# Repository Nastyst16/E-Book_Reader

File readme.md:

# OpenBook

## Project Overview
OpenBook is an open-source e-book reader designed to be cost-effective and accessible. The goal of this project is to develop the hardware required for mass production based on system architecture specifications. This includes designing the schematic, PCB layout, and 3D models necessary for the device.

## Repository Structure
```
- Hardware
  |-- schematic (.sch)
  |-- PCB layout (.brd)
- Manufacturing
  |-- gerbers.zip
  |-- Bill of Materials
  |-- Pick and Place file
- Mechanical
  |-- 3D model of the device (.step)
  |-- Fusion360 file of the complete device
- Images
  |-- Rendered images of the PCB and device
- LICENSE
- README.md
```

## Hardware Overview
### Block Diagram

# Bill of Materials (BOM)

| 🔩 Component                                        | 🔗 Link                | 📄 Datasheet                        |
|--------------------------------------------------|-----------------------------------|-----------------------------------|
| ESP32-C6 WROOM-1-N8                              | [SnapMagic](https://www.snapeda.com/parts/ESP32-C6-WROOM-1-N8/Espressif+Systems/view-part/?ref=eda)         | [Datasheet](https://www.snapeda.com/parts/ESP32-C6-WROOM-1-N8/Espressif%20Systems/datasheet/)     |
| ESP32C6 Varistor 1812                            | [Mouser](https://ro.mouser.com/ProductDetail/EPCOS-TDK/B72520T0350K062?qs=dEfas%2FXlABIszF52uu7vrg%3D%3D)        | [Datasheet](https://www.tdk-electronics.tdk.com/inf/75/db/CTVS_14/Surge_protection_series.pdf)     |
| ESP32 WROVER 0805 Capacitor                      | [Mouser](https://ro.mouser.com/ProductDetail/KYOCERA-AVX/SD0805S020S1R0?qs=jCA%252BPfw4LHbpkAoSnwrdjw%3D%3D)         | [Datasheet](https://ro.mouser.com/datasheet/2/40/schottky-3165252.pdf)     |
| ESP32 WROVER BME680 Sensor                       | [SnapMagic](https://www.snapeda.com/parts/BME680/Bosch/view-part/?welcome=home)        | [Datasheet](https://www.snapeda.com/parts/BME680/Bosch%20Sensortec/datasheet/)     |
| ESP32 WROVER MCP73831 Power Management           | [Mouser](https://eu.mouser.com/ProductDetail/Microchip-Technology/MCP73831T-2ACI-OT?qs=yUQqVecv4qvbBQBGbHx0Mw%3D%3D)         | [Datasheet](https://eu.mouser.com/datasheet/2/268/MCP73831_Family_Data_Sheet_DS20001984H-3441711.pdf)     || ESP32 WROVER P-Channel MOSFET                    | [Component Search Engine](https://componentsearchengine.com/part-view/DMG2305UX-7/Diodes%20Incorporated)         | [Datasheet](https://www.diodes.com//assets/Datasheets/DMG2305UX.pdf)     |
| LED Chip 0603                                    | [SnapMagic](https://www.snapeda.com/parts/KP-1608SURCK/Kingbright/view-part/?ref=search&t=LED%200603)        | [Datasheet](https://www.snapeda.com/parts/KP-1608SURCK/Kingbright/datasheet/)     |
| SJ                                               | [GrabCad](https://grabcad.com/library/solder-jumpers-1)         | [Datasheet](https://www.youtube.com/watch?v=dQw4w9WgXcQ)     |
| LTSPICE Resistor 0402                            | [Component Search Engine](https://componentsearchengine.com/part-view/R0402%201%25%20100%20K%20(RC0402FR-07100KL)/YAGEO)        | [Datasheet](https://www.yageo.com/upload/media/product/products/datasheet/rchip/PYu-RC_Group_51_RoHS_L_12.pdf)     |
| RCL CPOL 3528                                    | [SnapMagic](https://www.snapeda.com/parts/TAJB475K025RNJ/AVX/view-part/?ref=dk&t=capacitor%203528&con_ref=None)        | [Datasheet](https://s3.amazonaws.com/snapeda/datasheet/TAJB475K025RNJ_AVX.pdf)     |
| 112A-TAAR-R03                                    | [Comet](https://store.comet.srl.ro/Catalogue/Product/43497/)         | [Datasheet](https://store.comet.bg/download-file.php?id=27596)     |
| 744043680 IND                                    | [Mouser](https://eu.mouser.com/ProductDetail/Wurth-Elektronik/744043680?qs=PGXP4M47uW6VkZq%252BkzjrHA%3D%3D)        | [Datasheet](https://www.we-online.com/components/products/datasheet/744043680.pdf)     |
| BD5229G-TR                                       | [Component Search Engine](https://componentsearchengine.com/part-view/BD5229G-TR/ROHM%20Semiconductor)         | [Datasheet](https://datasheet.datasheetarchive.com/originals/distributors/Datasheets_SAMA/f2b9741ef86007909f138d561a359946.pdf)     |
| Custom Button                                    | [Panasonic](https://industry.panasonic.com/global/en/products/control/switch/light-touch/number/evqpuj02k)        | [Datasheet](https://industry.panasonic.com/global/en/downloads?tab=catalog&small_g_cd=203&part_no=EVQPUJ02K&q=RVZRUFVKMDJLJTdDMTMlN0MyMDMlN0MzNDU5JTdDMSU3QyU3QzIlN0M%3D)     |
| CPH3225A                                         | [SnapMagic](https://www.snapeda.com/parts/CPH3225A/Seiko+Instruments/view-part/?ref=eda)         | [Datasheet](https://www.snapeda.com/parts/CPH3225A/Seiko%20Instruments/datasheet/)     |
| DS3231SN RTC                                     | [SnapMagic](https://www.snapeda.com/parts/DS3231SN%23/Analog+Devices/view-part/?ref=eda)        | [Datasheet](https://www.snapeda.com/parts/DS3231SN%23/Analog%20Devices/datasheet/)     |
| FH34SRJ-24S-0.5SH Connector                      | [Component Search Engine](https://componentsearchengine.com/part-view/FH34SRJ-24S-0.5SH(99)/Hirose)        | [Datasheet](https://www.hirose.com/en/product/document?clcode=CL0580-1255-6-99&productname=FH34SRJ-24S-0.5SH(99)&series=FH34SRJ&documenttype=2DDrawing&lang=en&documentid=0000990903)     |
| MAX17048G+T10 Battery Fuel Gauge                 | [SnapMagic](https://www.snapeda.com/parts/MAX17048G+T10/Analog+Devices/view-part/?ref=eda)         | [Datasheet](https://www.snapeda.com/parts/MAX17048G+T10/Analog%20Devices/datasheet/)     |
| MBR0530 Schottky Diode                           | [SnapMagic](https://www.snapeda.com/parts/MBR0530/Onsemi/view-part/?ref=eda)        | [Datasheet](https://www.snapeda.com/parts/MBR0530/ON%20Semiconductor/datasheet/)     |
| PGB1010603MR Inductor                            | [SnapMagic](https://www.snapeda.com/parts/PGB1010603MR/Littelfuse/view-part/?ref=eda)         | [Datasheet](https://www.snapeda.com/parts/PGB1010603MR/Littelfuse%20Inc./datasheet/)     |
| QWIIC Connector                                  | [Mouser](https://eu.mouser.com/ProductDetail/Adafruit/4208?qs=PzGy0jfpSMtbScLbr0L5dw%3D%3D)        | [Datasheet](https://www.youtube.com/watch?v=dQw4w9WgXcQ)     |
| USB4110-GF-A USB Hub                             | [Component Search Engine](https://componentsearchengine.com/part-view/USB4110-GF-A/GCT%20(GLOBAL%20CONNECTOR%20TECHNOLOGY))         | [Datasheet](https://gct.co/files/drawings/usb4110.pdf)     |
| SI1308EDL-T1-GE3 MOSFET                          | [SnapMagic](https://www.snapeda.com/parts/SI1308EDL-T1-GE3/Vishay+Siliconix/view-part/?ref=eda)        | [Datasheet](https://www.youtube.com/watch?v=dQw4w9WgXcQ)     |
| TPTP20R                                          | [Comet](https://easyeda.com/component/7524403feb2642ac9f9f26dfb93ceacf)         | [Datasheet](https://easyeda.com/component/7524403feb2642ac9f9f26dfb93ceacf)     |
| USBLC6-2SC6Y USB Surge Protection                | [SnapMagic](https://www.snapeda.com/parts/USBLC6-2SC6Y/STMicroelectronics/view-part/?ref=eda)        | [Datasheet](https://www.snapeda.com/parts/USBLC6-2SC6Y/STMicroelectronics/datasheet/)     |
| W25Q512JVEIQ Flash Memory                        | [SnapMagic](https://www.snapeda.com/parts/W25Q512JVEIQ/Winbond+Electronics/view-part/?ref=eda)         | [Datasheet](https://www.snapeda.com/parts/W25Q512JVEIQ/Winbond%20Electronics/datasheet/)     |
| XC6220A331MR-G Voltage Regulator                 | [Component Search Engine](https://componentsearchengine.com/part-view/XC6220A331MR-G/Torex)        | [Datasheet](https://product.torexsemi.com/system/files/series/xc6220.pdf)     |

# Hardware Functionality Overview

## 1. Battery
- **Model:** CELLEVIA BATTERIES LP584174  
- **Specifications:** 3.7V, 1800mAh  
- **Purpose:** Powers the entire device. The Li-Po battery is managed by a dedicated charging controller, which helps extend battery lifespan and provides protection against overcharging and deep discharge.

## 2. E-Paper Display
- **Model:** 7.5” e-Paper V2  
- **Revision:** 2.0 (2019/06/28)  
- **Description:** This display offers ultra-low power consumption, making it ideal for static text rendering. It communicates via an SPI interface and is powered through a low-dropout (LDO) voltage regulator.

## 3. ESP32 C6 Microcontroller
- **Function:** Acts as the main controller, handling communication between all peripherals including the display, sensors, storage modules, and more. It also provides Wi-Fi and Bluetooth connectivity.

## 4. BME688 Environmental Sensor
- **Interface:** I2C  
- **Functionality:** Measures temperature, humidity, pressure, and air quality. These readings can influence device behavior depending on environmental conditions.

## 5. RTC Module - DS3231SN
- **Interface:** I2C  
- **Purpose:** Maintains accurate date and time even when the device is powered off. Useful for timestamping, scheduling wake-ups, or saving user progress.

## 6. Li-Po Charging Controller - MCP73831T
- **Power Source:** USB-C  
- **Function:** Safely manages the charging of the Li-Po battery. Includes features that prevent overcharging and deep discharge. The USB-C port also allows for fast charging.

## 7. SD Card Module
- **Interface:** SPI  
- **Purpose:** Enables external file storage, such as e-books. It is essential for managing and accessing reading materials.

## 8. External NOR Flash (64MB)
- **Interface:** SPI  
- **Usage:** Provides additional memory space for application data and firmware.

## 9. Test Pads & Qwiic/Stemma QT Connectors
- **Functionality:** Test pads are used for debugging and quality control during development. The modular connectors support easy integration of sensors or peripherals over I2C or SPI.

## 10. LDO Voltage Regulator
- **Purpose:** Ensures a stable voltage supply to all hardware components, protecting them from fluctuations in input voltage.

---

## Communication Interfaces

- **GPIO:** Used for handling physical buttons such as power or reset.
- **USB-C:** Used for charging and PC connectivity.
- **I2C:** Connects components like the environmental sensor and RTC module.
- **SPI:** Used for high-speed data transfer with components like the display, SD card, and external flash.

---

# Power Consumption Overview

The following estimates reflect typical usage scenarios based on standard operating conditions.

## Battery
- **Voltage:** 3.7V  
- **Capacity:** 1800mAh  
- **Battery Life:** Varies based on power draw; under typical conditions, it can last several hours.

## ESP32 C6
- **Idle:** ~0.1mA  
- **Wi-Fi active:** ~200mA  
- **Bluetooth active:** ~150mA  
- **Max load:** ~350mA  
- **Estimated average:** 150mA

## E-Paper Display
- **Consumption during refresh:** 30–50mA  
- **Estimated average:** 40mA with infrequent updates

## BME688 Sensor
- **Typical draw:** 2mA

## DS3231SN RTC Module
- **Estimated draw:** 2mA

## MCP73831T Charger
- **Consumption during idle:** Negligible

## SD Card
- **Typical draw:** 10–15mA  
- **Estimated average:** 12mA

## NOR Flash
- **Active usage:** 20–30mA  
- **Estimated average:** 25mA

---

## Estimated Total Consumption (Typical Use)

| Component              | Current Draw (mA) |
|------------------------|-------------------|
| ESP32 (Wi-Fi active)   | 200mA             |
| E-Paper Display        | 40mA              |
| BME688 Sensor          | 2mA               |
| RTC Module             | 2mA               |
| SD Card                | 12mA              |
| NOR Flash              | 25mA              |
| **Total**              | **281mA**         |

---

## Battery Life Estimate

To estimate battery life:

 - Battery Life = Battery Capacity / Average Current Draw
 - Battery Life = 1800mAh / 281mA ≈ 6.41 hours

 ### Important Notes:
This estimate assumes continuous operation with Wi-Fi enabled, periodic display refreshes, and sensor readings. In practical use, battery life can be significantly extended through:

- Low-power sleep modes on the ESP32  
- Reducing display update frequency  
- Disabling unused modules or interfaces 

# ESP32-C6 Pin Usage Breakdown

This section outlines the pin configuration used in the current hardware design based on the ESP32-C6 microcontroller.

## Power Connections
- **3V3 (Pin 2 & top-right corner)** – Supplies 3.3V to the microcontroller and all connected peripherals.
- **GND (bottom-right corner)** – Ground reference for the entire system.

## Boot and Reset
- **GPIO8 (Pin 15, IO/BOOT)** – Used to enter bootloader mode; pulled low through a 10kΩ resistor.
- **RESET (Pin 3)** – Manual reset input for restarting the microcontroller.

## SPI Interface (E-Paper Display and Flash Memory)
- **MISO (Pin 27)** – SPI Master-In Slave-Out; receives data from connected devices.
- **MOSI (Pin 10)** – SPI Master-Out Slave-In; sends data to peripherals.
- **SCK (Pin 7)** – Serial clock line for SPI communication.
- **SS_SD (Pin 4)** – Likely used as Chip Select (CS) for the SD card module.
- **EPD_CS (Pin 11)** – Chip Select for the E-Paper Display.
- **FLASH_CS (Pin 12)** – Chip Select for the external NOR Flash.

## E-Paper Display Control
- **EPD_BUSY (Pin 26)** – Indicates when the display controller is processing a command.
- **EPD_DC (Pin 5)** – Data/Command control signal for the E-Paper interface.
- **EPD_RST (Pin 21)** – Reset pin for the E-Paper controller.
- **EPD_3V3_C (Pin 19)** – Likely used to control or enable power to the E-Paper display.

## I2C Interface (RTC and Environmental Sensors)
- **SDA (Pin 20)** – Data line for I2C communication.
- **SCL (Pin 21)** – Clock line for I2C communication.
- **I2C_PW (Pin 18)** – Controls power delivery to I2C-connected devices.
- **INT_RTC (Pin 8)** – Interrupt output from the RTC module.
- **RTC_RST (Pin 16)** – Reset input for the RTC chip.

## USB Interface
- **USB_D- (Pin 13)** and **USB_D+ (Pin 14)** – Differential data lines for USB communication.

## UART Interface
- **TX (Pin 25)** – UART transmit pin used for serial output.
- **RX (Pin 24)** – UART receive pin used for serial input.

## Additional GPIOs
- **IO_CHANGE (Pin 23)** – Custom GPIO, possibly used for interrupts or status signals from external hardware.

---

### Pin Mapping Considerations

This pin configuration is chosen to balance performance and modularity:
- The SPI bus supports high-speed data exchange with both the E-Paper Display and external flash memory.
- The I2C bus is reserved for lower-speed peripherals, such as the RTC and environmental sensors.
- Dedicated control signals for the display enable precise handling of rendering operations.
- UART is available for serial debugging or external communication.
- Power, reset, and enable signals are placed for ease of access and stability in the overall system layout.

## Design Constraints
- **PCB Dimensions**: Must fit within the predefined casing
- **Power Traces**: Width = 0.3mm, Data traces = 0.15mm minimum
- **No Right-Angle Traces**: Ensure smooth signal flow
- **Decoupling Capacitors**: 100nF placed near power pins
- **ESP32 Antenna Placement**: Must be at the PCB edge, with no ground plane underneath

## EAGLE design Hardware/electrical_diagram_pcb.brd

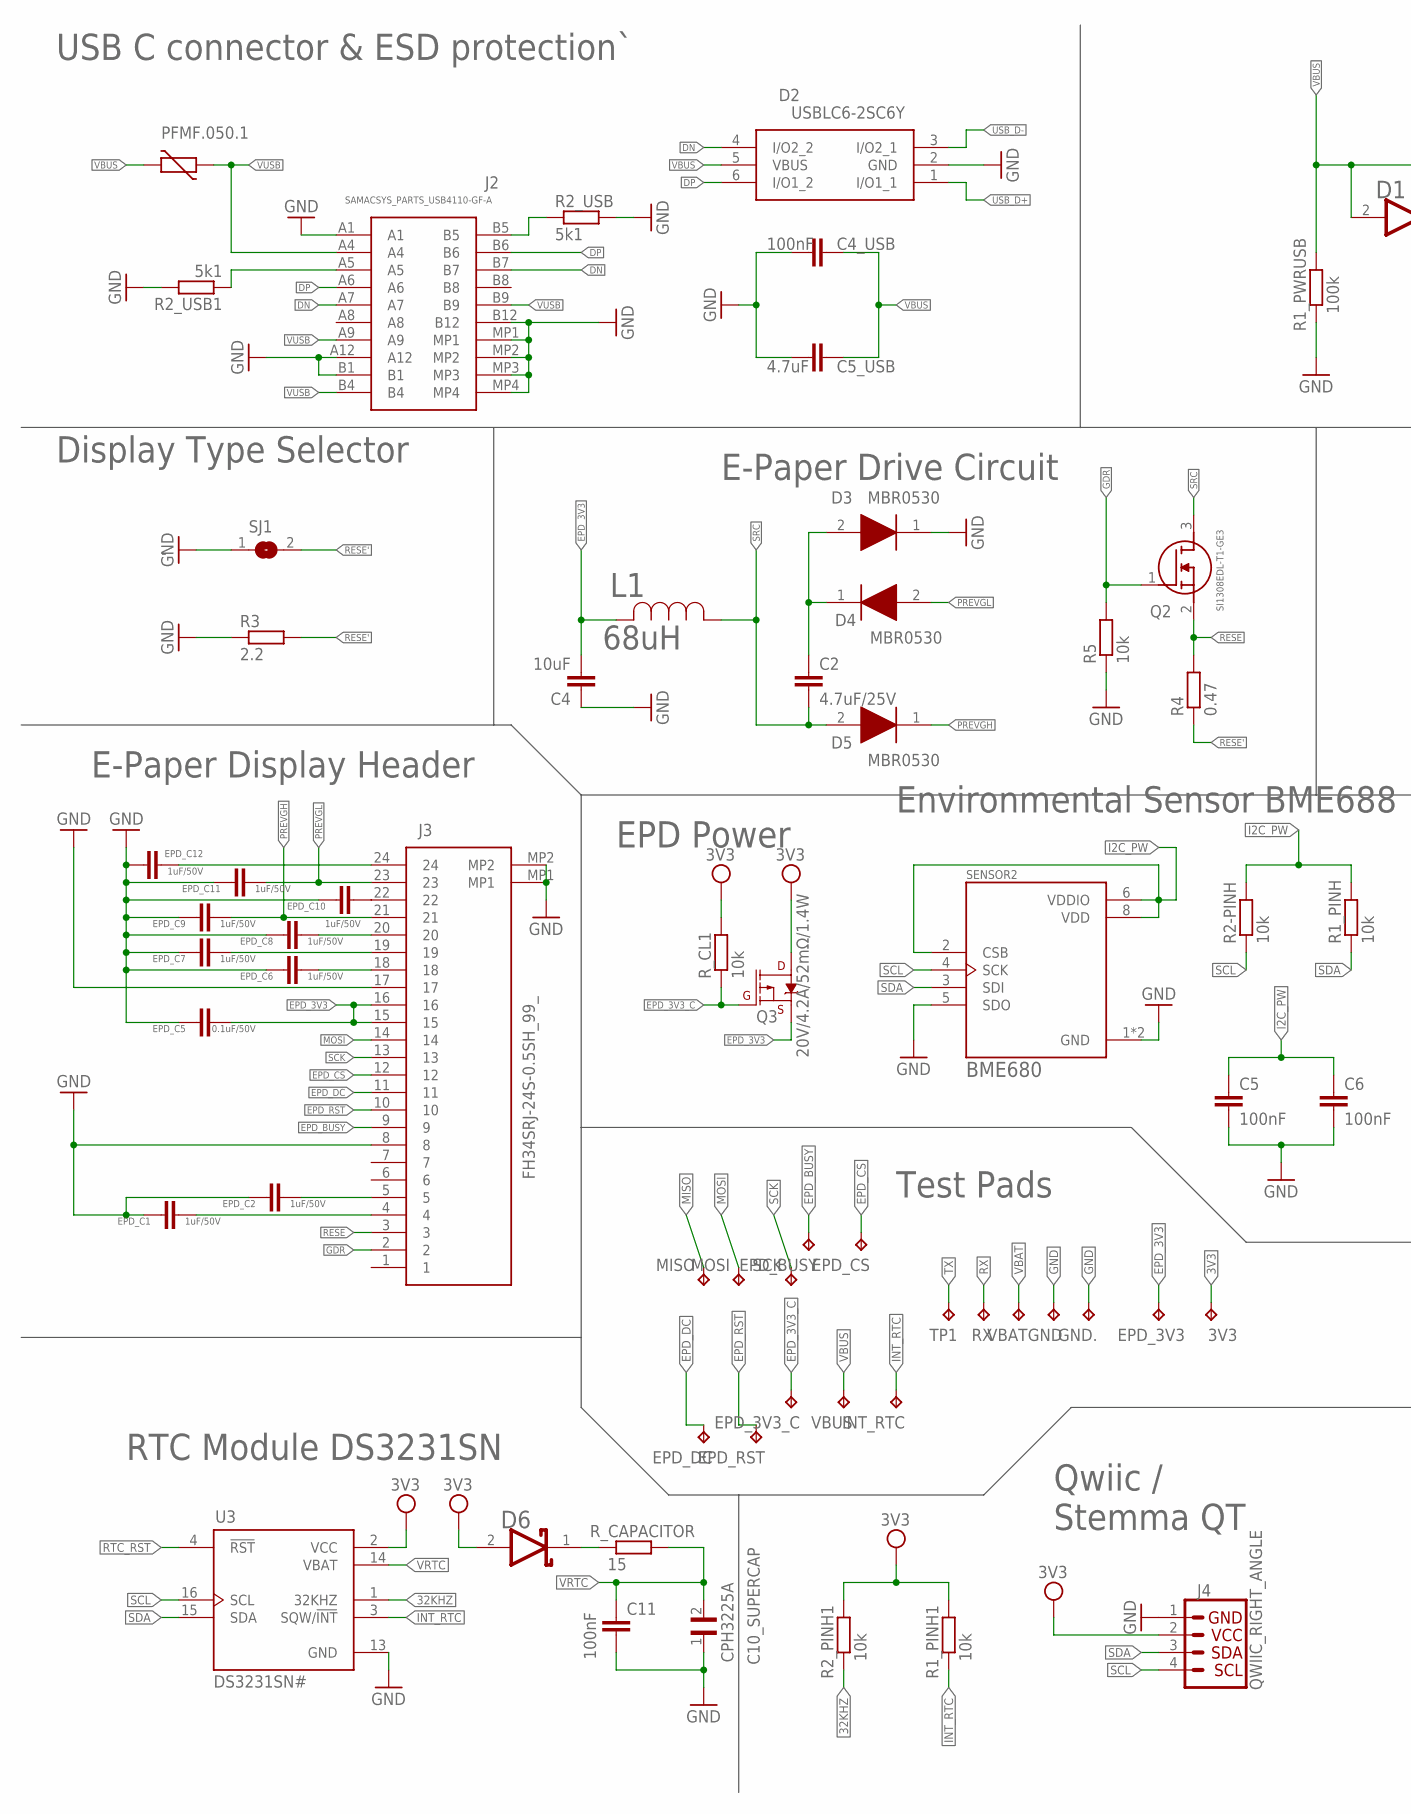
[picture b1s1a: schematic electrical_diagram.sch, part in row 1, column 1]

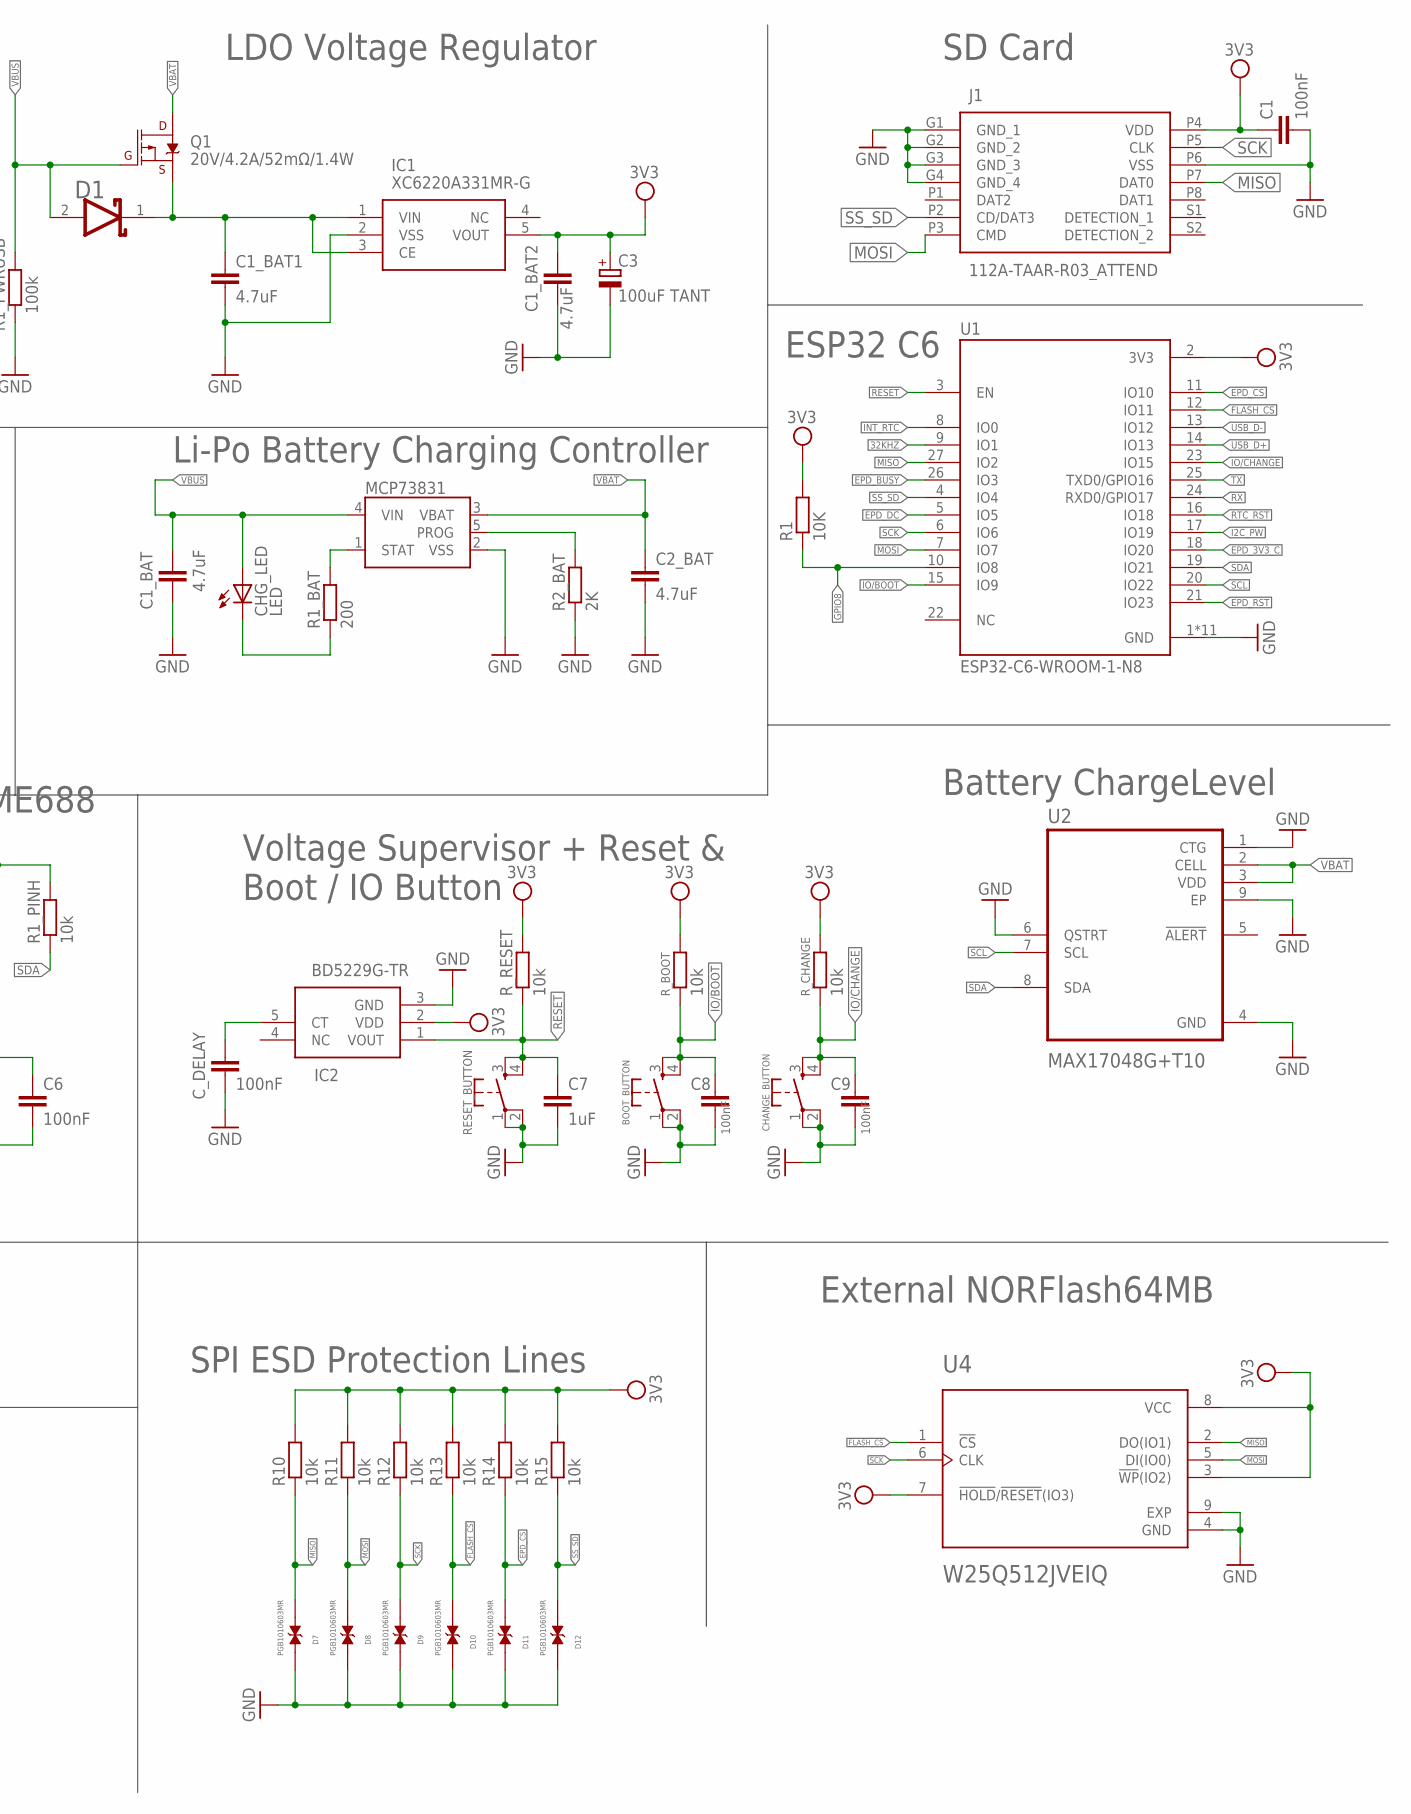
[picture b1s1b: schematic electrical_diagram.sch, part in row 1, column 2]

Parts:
3V3: TP; TP20R
BOOT_BUTTON: BUTTON_CUSYOMV1; MYBUTTON
C1, C4_USB: 100nF; EAGLE-LTSPICE_C0402
C1_BAT, C1_BAT1, C1_BAT2, C2_BAT, C5_USB: 4.7uF; EAGLE-LTSPICE_C0402
C2: 4.7uF/25V; EAGLE-LTSPICE_C0402
C3: 100uF TANT; RCL_CT3528
C4: 10uF; EAGLE-LTSPICE_C0402
C5, C6, C8, C9, C11: 100nF; ESP32_WROVER_EAGLE-LTSPICE_C0402
C7: 1uF; ESP32_WROVER_EAGLE-LTSPICE_C0402
C10_SUPERCAP: CPH3225A; CAPCP3225X100N
CHANGE_BUTTON: BUTTON_CUSYOMV1; MYBUTTON
CHG_LED: LED; ADAFRUIT_CHIP-LED0603
C_DELAY: 100nF; ESP32_WROVER_EAGLE-LTSPICE_C0402
D1, D6: ESP32_WROVER_AVX---SD0805S020S1R0_AVX_SD0805S020S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; ESP32_WROVER_AVX---SD0805S020S1R0_AVX_SD0805S020S1R0_0
D2: USBLC6-2SC6Y; SOT95P280X145-6N
D3, D4, D5: MBR0530; SOD3716X135N
D7, D8, D9, D10, D11, D12: PGB1010603MR; DIOC1608X36N
EPD_3V3, EPD_3V3_C: TP; TP20R
EPD_BUSY: TP; TP20R
EPD_C1, EPD_C2, EPD_C6, EPD_C7, EPD_C8, EPD_C9, EPD_C10, EPD_C11, EPD_C12: 1uF/50V; EAGLE-LTSPICE_C0402
EPD_C5: 0.1uF/50V; EAGLE-LTSPICE_C0402
EPD_CS: TP; TP20R
EPD_DC: TP; TP20R
EPD_RST: TP; TP20R
GND, GND.: TP; TP20R
IC1: XC6220A331MR-G; SOT95P280X120-5N
IC2: BD5229G-TR; SOT95P280X125-5N
INT_RTC: TP; TP20R
J1: 112A-TAAR-R03_ATTEND; 112ATAARR03ATTEND
J2: SAMACSYS_PARTS_USB4110-GF-A; SAMACSYS_PARTS_USB4110GFA
J3: FH34SRJ-24S-0.5SH_99_; FH34SRJ24S05SH99
J4: QWIIC_RIGHT_ANGLE; JST04_1MM_RA
L1: 68uH; IND_4828-WE-TPC_WRE
MCP73831: ESP32_WROVER_SPARKFUN-IC-POWER_MCP73831; ESP32_WROVER_SPARKFUN-IC-POWER_SOT23-5
MISO: TP; TP20R
MOSI: TP; TP20R
PFMF.050.1: ESP32C6_VARISTORCN1812; ESP32C6_VARISTOR_CT/CN1812
Q1, Q3: 20V/4.2A/52mΩ/1.4W; ESP32_WROVER_SPARKFUN-DISCRETESEMI_SOT23-3
Q2: SI1308EDL-T1-GE3; SOT65P210X110-3N
R1: 10K; ESP32_WROVER_EAGLE-LTSPICE_R0402
R1_BAT: 200; ESP32_WROVER_EAGLE-LTSPICE_R0402
R1_PINH, R1_PINH1, R2-PINH, R2_PINH1, R5, R10, R11, R12, R13, R14, R15: 10k; ESP32_WROVER_EAGLE-LTSPICE_R0402
R1_PWRUSB: 100k; ESP32_WROVER_EAGLE-LTSPICE_R0402
R2_BAT: 2K; ESP32_WROVER_EAGLE-LTSPICE_R0402
R2_USB, R2_USB1: 5k1; ESP32_WROVER_EAGLE-LTSPICE_R0402
R3: 2.2; ESP32_WROVER_EAGLE-LTSPICE_R0402
R4: 0.47; ESP32_WROVER_EAGLE-LTSPICE_R0402
RESET_BUTTON: BUTTON_CUSYOMV1; MYBUTTON
RX: TP; TP20R
R_BOOT: 10k; ESP32_WROVER_EAGLE-LTSPICE_R0402
R_CAPACITOR: 15; ESP32_WROVER_EAGLE-LTSPICE_R0402
R_CHANGE: 10k; ESP32_WROVER_EAGLE-LTSPICE_R0402
R_CL1: 10k; ESP32_WROVER_EAGLE-LTSPICE_R0402
R_RESET: 10k; ESP32_WROVER_EAGLE-LTSPICE_R0402
SCK: TP; TP20R
SENSOR2: BME680; ESP32_WROVER_BME680_PSON80P300X300X100-8N
SJ1: -; SJ
TP1: TP; TP20R
U1: ESP32-C6-WROOM-1-N8; XCVR_ESP32-C6-WROOM-1-N8
U2: MAX17048G+T10; SON50P200X200X80-9N
U3: DS3231SN#; SOIC127P1032X265-16N
U4: W25Q512JVEIQ; SON127P600X800X80-9N
VBAT: TP; TP20R
VBUS: TP; TP20R

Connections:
3V3: 3V3.TP, C1.1, C1_BAT2.1, C3.+, D6.2 (ANODE), IC1.5 (VOUT), IC2.2 (VDD), J1.P4 (VDD), J4.2, Q3.3 (D), R1.2, R1_PINH1.2, R2_PINH1.2, R10.2, R11.2, R12.2, R13.2, R14.2, R15.2, R_BOOT.2, R_CHANGE.2, R_CL1.2, R_RESET.2, U1.2 (3V3), U3.2 (VCC), U4.3 (!WP!(IO2)), U4.7 (!HOLD!/!RESET!(IO3)), U4.8 (VCC)
32KHZ: R2_PINH1.1, U1.9 (IO1), U3.1 (32KHZ)
DN: D2.4 (I/O2_2), J2.A7, J2.B7
DP: D2.6 (I/O1_2), J2.A6, J2.B6
EPD_3V3: C4.2, EPD_3V3.TP, EPD_C5.2, J3.15, J3.16, L1.2, Q3.2 (S)
EPD_3V3_C: EPD_3V3_C.TP, Q3.1 (G), R_CL1.1, U1.18 (IO20)
EPD_BUSY: EPD_BUSY.TP, J3.9, U1.26 (IO3)
EPD_CS: D11.1, EPD_CS.TP, J3.12, R14.1, U1.11 (IO10)
EPD_DC: EPD_DC.TP, J3.11, U1.5 (IO5)
EPD_RST: EPD_RST.TP, J3.10, U1.21 (IO23)
FLASH_CS: D10.1, R13.1, U1.12 (IO11), U4.1 (!CS)
GDR: J3.2, Q2.1 (G), R5.2
GND: BOOT_BUTTON.1, BOOT_BUTTON.2, C1.2, C1_BAT.2, C1_BAT1.2, C1_BAT2.2, C2_BAT.2, C3.-, C4.1, C4_USB.2, C5.2, C5_USB.2, C6.2, C7.2, C8.2, C9.2, C10_SUPERCAP.1, C11.2, CHANGE_BUTTON.1, CHANGE_BUTTON.2, C_DELAY.2, D2.2 (GND), D3.1 (K), D7.2, D8.2, D9.2, D10.2, D11.2, D12.2, EPD_C1.1, EPD_C2.1, EPD_C5.1, EPD_C6.1, EPD_C7.1, EPD_C8.1, EPD_C9.1, EPD_C10.1, EPD_C11.1, EPD_C12.1, GND.TP, GND..TP, IC1.2 (VSS), IC2.3 (GND), J1.G1 (GND_1), J1.G2 (GND_2), J1.G3 (GND_3), J1.G4 (GND_4), J1.P6 (VSS), J2.A1, J2.A12, J2.B1, J2.B12, J2.MP1, J2.MP2, J2.MP3, J2.MP4, J3.8, J3.17, J3.MP1, J3.MP2, J4.1, MCP73831.2 (VSS), R1_PWRUSB.1, R2_BAT.1, R2_USB.2, R2_USB1.2, R3.1, R5.1, RESET_BUTTON.1, RESET_BUTTON.2, SENSOR2.1 (GND), SENSOR2.5 (SDO), SENSOR2.7 (GND), SJ1.1, U1.1 (GND), U1.28 (GND), U1.29_1 (GND), U1.29_2 (GND), U1.29_3 (GND), U1.29_4 (GND), U1.29_5 (GND), U1.29_6 (GND), U1.29_7 (GND), U1.29_8 (GND), U1.29_9 (GND), U2.1 (CTG), U2.4 (GND), U2.6 (QSTRT), U2.9 (EP), U3.13 (GND), U4.4 (GND), U4.9 (EXP)
GPIO8: R1.1, U1.10 (IO8)
I2C_PW: C5.1, C6.1, R1_PINH.2, R2-PINH.2, SENSOR2.2 (CSB), SENSOR2.6 (VDDIO), SENSOR2.8 (VDD), U1.17 (IO19)
INT_RTC: INT_RTC.TP, R1_PINH1.1, U1.8 (IO0), U3.3 (SQW/!INT)
IO/BOOT: BOOT_BUTTON.3, BOOT_BUTTON.4, C8.1, R_BOOT.1, U1.15 (IO9)
IO/CHANGE: C9.1, CHANGE_BUTTON.3, CHANGE_BUTTON.4, R_CHANGE.1, U1.23 (IO15)
MISO: D7.1, J1.P7 (DAT0), MISO.TP, R10.1, U1.27 (IO2), U4.2 (DO(IO1))
MOSI: D8.1, J1.P3 (CMD), J3.14, MOSI.TP, R11.1, U1.7 (IO7), U4.5 (DI(IO0))
unnamed: C_DELAY.1, IC2.5 (CT)
unnamed: D6.1 (CATHODE), R_CAPACITOR.1
unnamed: C1_BAT1.1, D1.1 (CATHODE), IC1.1 (VIN), IC1.3 (CE), Q1.2 (S)
unnamed: J2.B5, R2_USB.1
unnamed: J2.A5, R2_USB1.1
unnamed: MCP73831.1 (STAT), R1_BAT.2
unnamed: C2.1, D3.2 (A), D4.1 (K)
unnamed: CHG_LED.C, R1_BAT.1
unnamed: MCP73831.5 (PROG), R2_BAT.2
unnamed: EPD_C6.2, J3.18
unnamed: EPD_C7.2, J3.19
unnamed: EPD_C8.2, J3.20
unnamed: EPD_C1.2, J3.4
unnamed: EPD_C10.2, J3.22
unnamed: EPD_C12.2, J3.24
unnamed: EPD_C2.2, J3.5
PREVGH: D5.1 (K), EPD_C9.2, J3.21
PREVGL: D4.2 (A), EPD_C11.2, J3.23
RESE: J3.3, Q2.2 (S), R4.2
RESE': R3.2, R4.1, SJ1.2
RESET: C7.1, IC2.1 (VOUT), RESET_BUTTON.3, RESET_BUTTON.4, R_RESET.1, U1.3 (EN)
RTC_RST: U1.16 (IO18), U3.4 (!RST)
RX: RX.TP, U1.24 (RXD0/GPIO17)
SCK: D9.1, J1.P5 (CLK), J3.13, R12.1, SCK.TP, U1.6 (IO6), U4.6 (CLK)
SCL: J4.4, R2-PINH.1, SENSOR2.4 (SCK), U1.20 (IO22), U2.7 (SCL), U3.16 (SCL)
SDA: J4.3, R1_PINH.1, SENSOR2.3 (SDI), U1.19 (IO21), U2.8 (SDA), U3.15 (SDA)
SRC: C2.2, D5.2 (A), L1.1, Q2.3 (D)
SS_SD: D12.1, J1.P2 (CD/DAT3), R15.1, U1.4 (IO4)
TX: TP1.TP, U1.25 (TXD0/GPIO16)
USB_D+: D2.1 (I/O1_1), U1.14 (IO13)
USB_D-: D2.3 (I/O2_1), U1.13 (IO12)
VBAT: C2_BAT.1, MCP73831.3 (VBAT), Q1.3 (D), U2.2 (CELL), U2.3 (VDD), VBAT.TP
VBUS: C1_BAT.1, C4_USB.1, C5_USB.1, CHG_LED.A, D1.2 (ANODE), D2.5 (VBUS), MCP73831.4 (VIN), PFMF.050.1.2, Q1.1 (G), R1_PWRUSB.2, VBUS.TP
VRTC: C10_SUPERCAP.2, C11.1, R_CAPACITOR.2, U3.14 (VBAT)
VUSB: J2.A4, J2.A9, J2.B4, J2.B9, PFMF.050.1.1

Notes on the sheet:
USB C connector & ESD protection`
Display Type Selector
E-Paper Drive Circuit
LDO Voltage Regulator
SD Card
ESP32 C6
Li-Po Battery Charging Controller
E-Paper Display Header
EPD Power
Environmental Sensor BME688
Voltage Supervisor + Reset & Boot / IO Button
Battery ChargeLevel
External NORFlash64MB
SPI ESD Protection Lines
Qwiic / Stemma QT
Test Pads
RTC Module DS3231SN

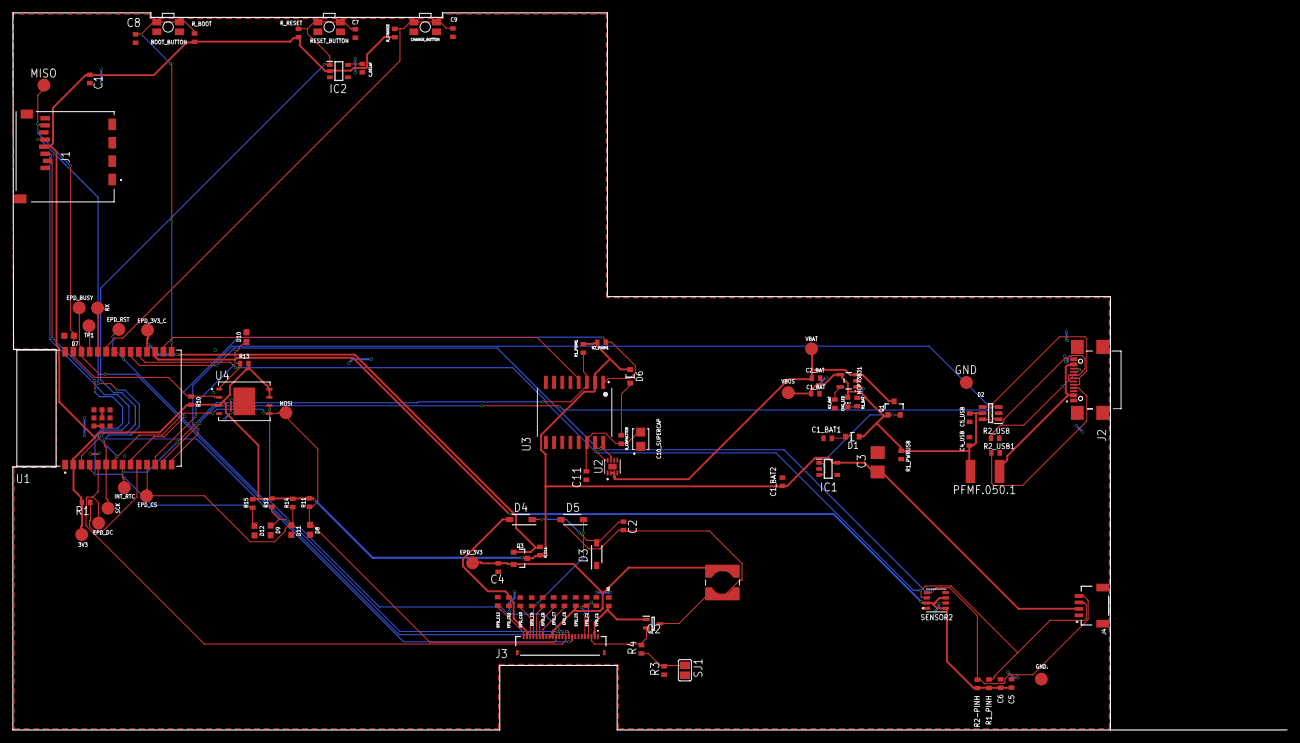
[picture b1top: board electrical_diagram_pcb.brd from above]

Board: 2 copper layers, 170.2 x 111.2 mm, 103 parts (0 on the bottom side), 55 nets.

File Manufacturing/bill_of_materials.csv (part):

Qty,Value,Device,Package,Parts,Description,ARROW_PART_NUMBER,ARROW_PRICE-STOCK,AVAILABILITY,CENTROID_NOT_SPECIFIED,CHECK_PRICES,COPYRIGHT,DATASHEET,DESCRIPTION,DIGIKEY_DESCRIPTION,DIGIKEY_PART_NUMBER,HEIGHT,LEAD_FREE,MANUFACTURER_NAME,MANUFACTURER_PART_NUMBER,MF,MFR_NAME,MOUSER_PART_NUMBER,MOUSER_PRICE-STOCK,MOUSER_TESTING_PART_NUMBER,MOUSER_TESTING_PRICE-STOCK,MP,MPN,PACKAGE,POPULARITY,PREFIX,PRICE,PROD_ID,PURCHASE-URL,ROHS,SNAPEDA_LINK,SPICEMODEL,SPICEPREFIX,TEMPERATURE_RANGE_HIGH,TEMPERATURE_RANGE_LOW,VALUE
1,,ADAFRUIT_LEDCHIP-LED0603,ADAFRUIT_CHIP-LED0603,CHG_LED,LED,,,,,,,,,,,,,,,,,,,,,,,,,,,,,,,,,,,
1,,SJ,SJ,SJ1,"SMD solder JUMPER",,,,,,,,,,,,,,,,,,,,,,,,3,,,,,,,,,,,
1,0.1uF/50V,EAGLE-LTSPICE_C,EAGLE-LTSPICE_C0402,EPD_C5,"CAPACITOR, European symbol",,,,,,,,,,,,,,,,,,,,,,,,,,,,,,,,,,,
1,0.47,ESP32_WROVER_EAGLE-LTSPICE_R,ESP32_WROVER_EAGLE-LTSPICE_R0402,R4,"RESISTOR, European symbol",,,,,,,,,,,,,,,,,,,,,,,,,,,,,,,,,,,
1,100k,ESP32_WROVER_EAGLE-LTSPICE_R,ESP32_WROVER_EAGLE-LTSPICE_R0402,R1_PWRUSB,"RESISTOR, European symbol",,,,,,,,,,,,,,,,,,,,,,,,,,,,,,,,,,,
2,100nF,EAGLE-LTSPICE_C,EAGLE-LTSPICE_C0402,"C1, C4_USB","CAPACITOR, European symbol",,,,,,,,,,,,,,,,,,,,,,,,,,,,,,,,,,,
6,100nF,ESP32_WROVER_EAGLE-LTSPICE_CC0402,ESP32_WROVER_EAGLE-LTSPICE_C0402,"C5, C6, C8, C9, C11, C_DELAY","CAPACITOR, European symbol",,,,,,,,,,,,,,,,,,,,,,,,,,,,,,,NONE,C,,,
1,"100uF TANT",RCL_CPOL-EUCT3528,RCL_CT3528,C3,"POLARIZED CAPACITOR, European symbol",,,,,,,,,,,,,,,,,,,,,,,,0,,,,,,,,C,,,
1,10K,ESP32_WROVER_EAGLE-LTSPICE_R,ESP32_WROVER_EAGLE-LTSPICE_R0402,R1,"RESISTOR, European symbol",,,,,,,,,,,,,,,,,,,,,,,,,,,,,,,,,,,
15,10k,ESP32_WROVER_EAGLE-LTSPICE_R,ESP32_WROVER_EAGLE-LTSPICE_R0402,"R1_PINH, R1_PINH1, R2-PINH, R2_PINH1, R5, R10, R11, R12, R13, R14, R15, R_BOOT, R_CHANGE, R_CL1, R_RESET","RESISTOR, European symbol",,,,,,,,,,,,,,,,,,,,,,,,,,,,,,,,,,,
1,10uF,EAGLE-LTSPICE_C,EAGLE-LTSPICE_C0402,C4,"CAPACITOR, European symbol",,,,,,,,,,,,,,,,,,,,,,,,,,,,,,,,,,,
1,112A-TAAR-R03_ATTEND,112A-TAAR-R03_ATTEND,112ATAARR03ATTEND,J1,"Micro SD Card Socket, Push-Push Type, Top Mount, SMT, H=1.83mm, 10u",,,,,,,,"Micro SD Card Socket"," Push-Push Type"," Top Mount"," SMT"," H=1.83mm"," 10u",,,1.9mm,,ATTEND,"112A-TAAR-R03 ATTEND",,,,,,,,,,,,,,,,
1,15,ESP32_WROVER_EAGLE-LTSPICE_R,ESP32_WROVER_EAGLE-LTSPICE_R0402,R_CAPACITOR,"RESISTOR, European symbol",,,,,,,,,,,,,,,,,,,,,,,,,,,,,,,,,,,
1,1uF,ESP32_WROVER_EAGLE-LTSPICE_CC0402,ESP32_WROVER_EAGLE-LTSPICE_C0402,C7,"CAPACITOR, European symbol",,,,,,,,,,,,,,,,,,,,,,,,,,,,,,,NONE,C,,,
9,1uF/50V,EAGLE-LTSPICE_C,EAGLE-LTSPICE_C0402,"EPD_C1, EPD_C2, EPD_C6, EPD_C7, EPD_C8, EPD_C9, EPD_C10, EPD_C11, EPD_C12","CAPACITOR, European symbol",,,,,,,,,,,,,,,,,,,,,,,,,,,,,,,,,,,
1,2.2,ESP32_WROVER_EAGLE-LTSPICE_R,ESP32_WROVER_EAGLE-LTSPICE_R0402,R3,"RESISTOR, European symbol",,,,,,,,,,,,,,,,,,,,,,,,,,,,,,,,,,,
1,200,ESP32_WROVER_EAGLE-LTSPICE_R,ESP32_WROVER_EAGLE-LTSPICE_R0402,R1_BAT,"RESISTOR, European symbol",,,,,,,,,,,,,,,,,,,,,,,,,,,,,,,,,,,
2,20V/4.2A/52mO/1.4W,ESP32_WROVER_SPARKFUN-DISCRETESEMI_MOSFET_PCH-DMG2305UX-7,ESP32_WROVER_SPARKFUN-DISCRETESEMI_SOT23-3,"Q1, Q3","P-channel MOSFETs",,,,,,,,,,,,,,,,,,,,,,,,,,,TRAN-14388,,,,,,,,20V/4.2A/52mO/1.4W
1,2K,ESP32_WROVER_EAGLE-LTSPICE_R,ESP32_WROVER_EAGLE-LTSPICE_R0402,R2_BAT,"RESISTOR, European symbol",,,,,,,,,,,,,,,,,,,,,,,,,,,,,,,,,,,
5,4.7uF,EAGLE-LTSPICE_C,EAGLE-LTSPICE_C0402,"C1_BAT, C1_BAT1, C1_BAT2, C2_BAT, C5_USB","CAPACITOR, European symbol",,,,,,,,,,,,,,,,,,,,,,,,,,,,,,,,,,,
1,4.7uF/25V,EAGLE-LTSPICE_C,EAGLE-LTSPICE_C0402,C2,"CAPACITOR, European symbol",,,,,,,,,,,,,,,,,,,,,,,,,,,,,,,,,,,
2,5k1,ESP32_WROVER_EAGLE-LTSPICE_R,ESP32_WROVER_EAGLE-LTSPICE_R0402,"R2_USB, R2_USB1","RESISTOR, European symbol",,,,,,,,,,,,,,,,,,,,,,,,,,,,,,,,,,,
1,68uH,744043680IND_4828-WE-TPC_WRE,IND_4828-WE-TPC_WRE,L1,,,,,,,"Copyright (C) 2024 Ultra Librarian. All rights reserved.",,,,,,,,744043680,,"Wurth Electronics",,,,,,,,,,,,,,,,,,,
1,BD5229G-TR,BD5229G-TR,SOT95P280X125-5N,IC2,"Voltage Detector with Adjustable Delay Time: CMOS processes are utilized to develop high precision, low current consumption CMOS reset ICs that allow arbitrary setting of the delay time. The extensive lineup includes both Nch Open Drain and CMOS output types in a wide range of detection voltages (from 2.3V to 6.0V, in 0.1V steps), enabling selection of the ideal solution based on customer requirements. In addition, the entire series is of course both lead-free and RoHS-compliant.",,,,,,,,"Voltage Detector with Adjustable Delay Time: CMOS processes are utilized to develop high precision"," low current consumption CMOS reset ICs that allow arbitrary setting of the delay time. The extensive lineup includes both Nch Open Drain and CMOS output types in a wide range of detection voltages (from 2.3V to 6.0V"," in 0.1V steps)"," enabling selection of the ideal solution based on customer requirements. In addition"," the entire series is of course both lead-free and RoHS-compliant.",,,1.25mm,,"ROHM Semiconductor",BD5229G-TR,,,755-BD5229G-TR,https://www.mouser.co.uk/ProductDetail/ROHM-Semiconductor/BD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,,,,,,,,,,,,,
1,BME680,ESP32_WROVER_BME680_BME680,ESP32_WROVER_BME680_PSON80P300X300X100-8N,SENSOR2,"Integrated Environmental Unit",,,Unavailable,,,,," Integrated Environmental Unit ",,,,,,,"Bosch Sensortec",,,,,,BME680,,"LGA-8 Bosch Tools",,,None,,,,,,,,,
3,BUTTON_CUSYOMV1,BUTTON_CUSYOMV1,MYBUTTON,"BOOT_BUTTON, CHANGE_BUTTON, RESET_BUTTON",,,,,,,,,,,,,,,,,,,,,,,,,,,,,,,,,,,,
1,CPH3225A,CPH3225A,CAPCP3225X100N,C10_SUPERCAP,"Cap 0.011F 3.3V 1210 Flat Check availability",,,"Not in stock",,https://www.snapeda.com/parts/CPH3225A/Seiko+Instruments/vie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,,," 11 mF (EDLC) Supercapacitor 3.3 V 1210 (3225 Metric) - - ",,,,,,,"Seiko Instruments",,,,,,CPH3225A,,"1210 Seiko",,,None,,"https://www.snapeda.com/api/url_track_click_mouser/?unipart_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 Instruments&part_name=CPH3225A&search_term=None",,https://www.snapeda.com/parts/CPH3225A/Seiko+Instruments/vie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,,,,,
1,DS3231SN#,DS3231SN#,SOIC127P1032X265-16N,U3,"Real Time Clock Serial 16-Pin SOIC W T/R     Check availability",,,"In Stock",,https://www.snapeda.com/parts/DS3231SN%23/Analog+Devices/vie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,,," Extremely Accurate I²C-Integrated RTC/TCXO/Crystal ",,,,,,,"Analog Devices",,,,,,DS3231SN#,,"SOIC-16 Maxim",,,None,,"https://www.snapeda.com/api/url_track_click_mouser/?unipart_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 Devices&part_name=DS3231SN#&search_term=None",,https://www.snapeda.com/parts/DS3231SN%23/Analog+Devices/vie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,,,,,
1,ESP32-C6-WROOM-1-N8,ESP32-C6-WROOM-1-N8,XCVR_ESP32-C6-WROOM-1-N8,U1,"Check availability",,,"In Stock",,https://www.snapeda.com/parts/ESP32-C6-WROOM-1-N8/Espressif+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,,," Multiprotocol Modules ESP32-C6 module"," Wi-Fi 6 in 2.4 GHz band"," Bluetooth 5"," Zigbee 3.0 and Thread. ESP34-WROOM Compatible - ENGINEERING SAMPLE ",,,,,,,"Espressif Systems",,,,,,ESP32-C6-WROOM-1-N8,,None,,,None,,,,https://www.snapeda.com/parts/ESP32-C6-WROOM-1-N8/Espressif+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,,
1,ESP32C6_VARISTORCN1812,ESP32C6_VARISTORCN1812,ESP32C6_VARISTOR_CT/CN1812,PFMF.050.1,VARISTOR,,,,,,,,,,,,,,,,,,,,,,,,0,,,,,,,,,,,
2,ESP32_WROVER_AVX---SD0805S020S1R0_AVX_SD0805S020S1R0_0_0AVX_SD0805S020S1R0_0_0,ESP32_WROVER_AVX---SD0805S020S1R0_AVX_SD0805S020S1R0_0_0AVX_SD0805S020S1R0_0_0,ESP32_WROVER_AVX---SD0805S020S1R0_AVX_SD0805S020S1R0_0,"D1, D6","Schottky Barrier Rectifier Diode",,,,No,,,http://datasheets.avx.com/schottky.pdf,,"DIODE SCHOTTKY 20V 1A 0805",478-7800-1-ND,,yes,,,AVX,,581-SD0805S020S1R0,,,,,,"0805 (2012 metric)",,D,,,,yes,,,,+125°C,-55°C,
1,ESP32_WROVER_SPARKFUN-IC-POWER_MCP73831,ESP32_WROVER_SPARKFUN-IC-POWER_MCP73831,ESP32_WROVER_SPARKFUN-IC-POWER_SOT23-5,MCP73831,"MCP73831T Li-Ion, Li-Pol Controller",,,,,,,,,,,,,,,,,,,,,,,,,,,IC-09995,,,,,,,,
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
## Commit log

2025-04-05 proiect tsc
2025-04-06 Create LICENSE
2025-04-06 readme done
2025-04-14 issues solved

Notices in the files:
parts and their libraries:
DeskAssistant v19 v1: COPYRIGHT: Copyright (C) 2024 Ultra Librarian. All rights reserved.
